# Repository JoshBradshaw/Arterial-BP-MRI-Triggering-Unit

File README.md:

# Arterial-BP-MRI-Triggering-Unit
Full source code and schematics for an Arterial Blood Pressure Pulse MRI triggering unit

A full description of each major component of this project is available at the [project website](http://joshbradshaw.github.io/Arterial-BP-MRI-Triggering-Unit/)

# This device is an arterial blood presure triggering unit for retrospective gating in MRI imaging.

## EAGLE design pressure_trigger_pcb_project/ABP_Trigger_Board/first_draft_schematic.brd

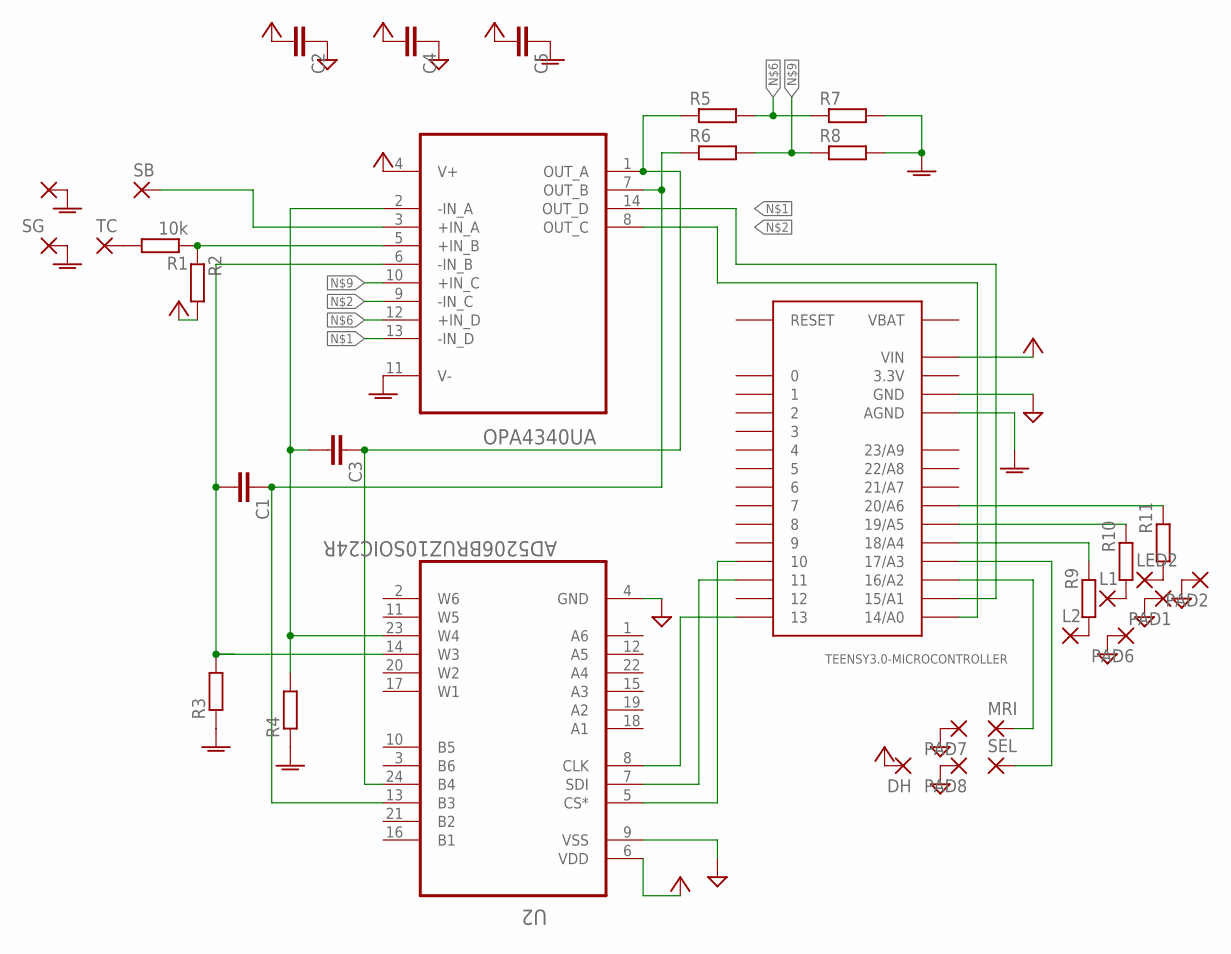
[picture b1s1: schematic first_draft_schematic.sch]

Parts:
C1, C3: 10pF; C0805
C2, C4, C5: 0.1uF; C0805
DH: WIREPAD1,6/0,9; 1,6/0,9
L1, L2: WIREPAD1,6/0,9; 1,6/0,9
LED2: WIREPAD1,6/0,9; 1,6/0,9
MRI: WIREPAD1,6/0,9; 1,6/0,9
PAD1, PAD2, PAD6, PAD7, PAD8: WIREPAD1,6/0,9; 1,6/0,9
R1, R2: 10k; R0805
R3, R4: 5k; R0805
R5, R6: 12k; R0805
R7, R8: 23.2k; R0805
R9, R10, R11: 681; R0805
SB: SAMBA; 1,6/0,9
SEL: WIREPAD1,6/0,9; 1,6/0,9
SG: WIREPAD1,6/0,9; 1,6/0,9
TC: WIREPAD1,6/0,9; 1,6/0,9
TEENSY3.0-MICROCONTROLLER: TEENSY_3.0_BASIC-PGM
TG: WIREPAD1,6/0,9; 1,6/0,9
U1: OPA4340UA; SOIC127P600X175-14N
U2: AD5206BRUZ10SOIC24R; SO24R

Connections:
3.3V: TEENSY3.0-MICROCONTROLLER.3.3V, TEENSY3.0-MICROCONTROLLER.3.3V1 (3.3V)
AGND: C5.1, R3.1, R4.1, R7.2, R8.2, SG.1, TEENSY3.0-MICROCONTROLLER.AGND, TG.1, U1.11 (V-)
GND: C2.1, C4.1, PAD1.1, PAD2.1, PAD6.1, PAD7.1, PAD8.1, TEENSY3.0-MICROCONTROLLER.GND, TEENSY3.0-MICROCONTROLLER.GND1 (GND), U2.4 (GND), U2.9 (VSS)
unnamed: TEENSY3.0-MICROCONTROLLER.15/A1, U1.13 (-IN_D), U1.14 (OUT_D)
unnamed: TEENSY3.0-MICROCONTROLLER.14/A0, U1.8 (OUT_C), U1.9 (-IN_C)
unnamed: C3.2, R4.2, U1.2 (-IN_A), U2.23 (W4)
unnamed: R1.1, R2.1, U1.5 (+IN_B)
unnamed: C3.1, R5.1, U1.1 (OUT_A), U2.24 (B4)
unnamed: R5.2, R7.1, U1.12 (+IN_D)
unnamed: TEENSY3.0-MICROCONTROLLER.10, U2.5 (CS*)
unnamed: TEENSY3.0-MICROCONTROLLER.11, U2.7 (SDI)
unnamed: R6.2, R8.1, U1.10 (+IN_C)
unnamed: SB.1, U1.3 (+IN_A)
unnamed: L2.1, R9.1
unnamed: C1.2, R3.2, U1.6 (-IN_B), U2.14 (W3)
unnamed: R1.2, TC.1
unnamed: R9.2, TEENSY3.0-MICROCONTROLLER.18/A4
unnamed: MRI.1, TEENSY3.0-MICROCONTROLLER.16/A2
unnamed: SEL.1, TEENSY3.0-MICROCONTROLLER.17/A3
unnamed: C1.1, R6.1, U1.7 (OUT_B), U2.13 (B3)
unnamed: L1.1, R10.1
unnamed: TEENSY3.0-MICROCONTROLLER.13, U2.8 (CLK)
unnamed: R10.2, TEENSY3.0-MICROCONTROLLER.19/A5
unnamed: LED2.1, R11.1
unnamed: R11.2, TEENSY3.0-MICROCONTROLLER.20/A6
VBAT: TEENSY3.0-MICROCONTROLLER.VBAT
VCC: C2.2, C4.2, C5.2, DH.1, R2.2, TEENSY3.0-MICROCONTROLLER.VIN, U1.4 (V+), U2.6 (VDD)

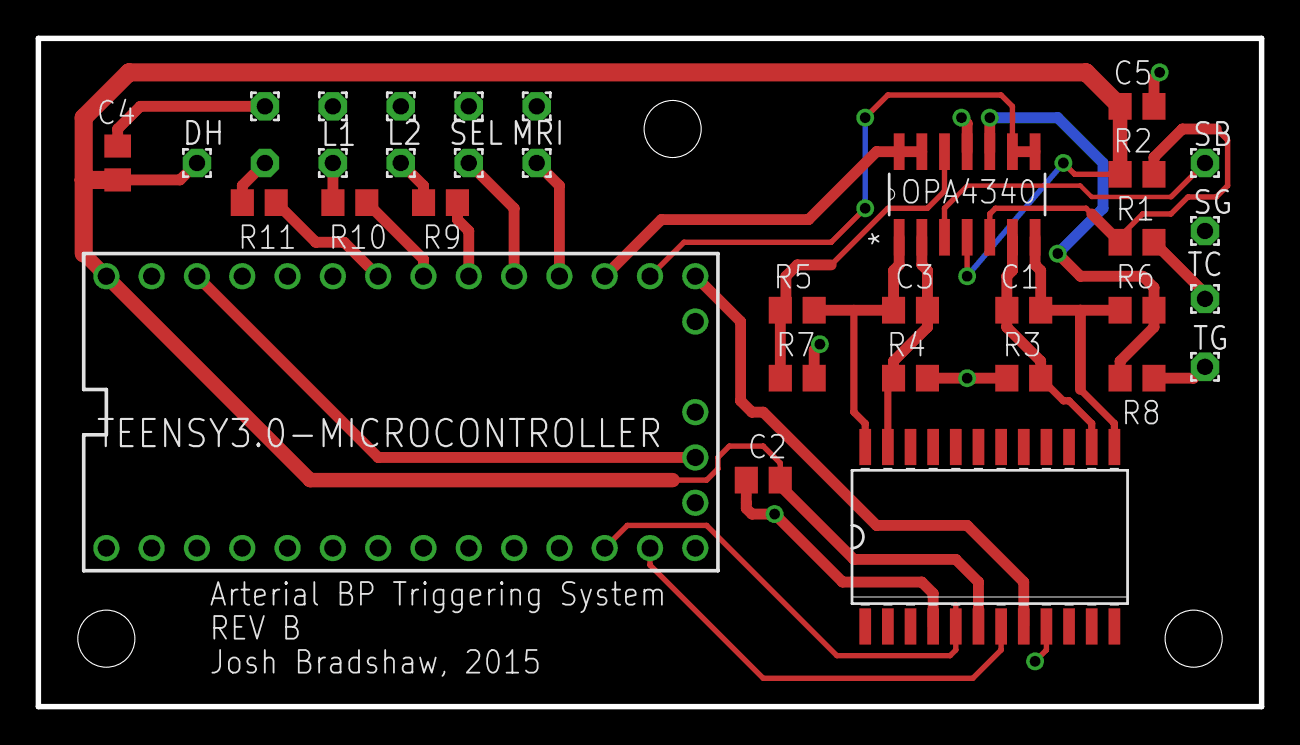
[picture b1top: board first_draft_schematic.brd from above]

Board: 2 copper layers, 68.6 x 37.5 mm, 34 parts (1 on the bottom side), 26 nets.

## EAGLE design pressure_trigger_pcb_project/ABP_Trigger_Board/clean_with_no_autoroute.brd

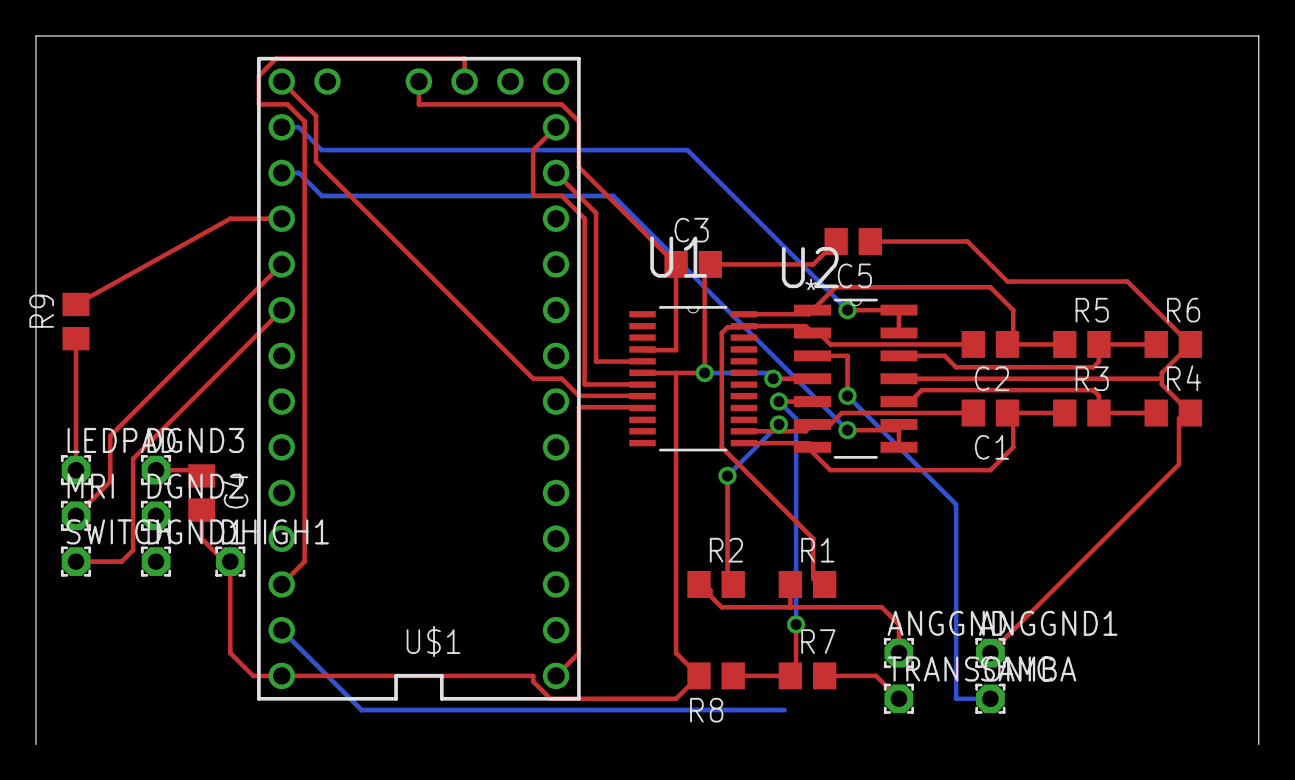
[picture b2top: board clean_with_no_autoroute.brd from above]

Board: 2 copper layers, 67.9 x 39.4 mm, 28 parts (0 on the bottom side), 22 nets.

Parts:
ANGGND, ANGGND1: WIREPAD1,6/0,9; 1,6/0,9
C1, C2: 10pF; C0805
C3, C4, C5: 0.1uF; C0805
DGND1, DGND2, DGND3: WIREPAD1,6/0,9; 1,6/0,9
DHIGH1: WIREPAD1,6/0,9; 1,6/0,9
LEDPAD: WIREPAD1,6/0,9; 1,6/0,9
MRI: WIREPAD1,6/0,9; 1,6/0,9
R1, R2: 5k; R0805
R3, R5: 12k; R0805
R4, R6: 23.2k; R0805
R7, R8: 10k; R0805
R9: 681; R0805
SAMBA: SAMBA; 1,6/0,9
SWITCH: WIREPAD1,6/0,9; 1,6/0,9
TRANSONIC: WIREPAD1,6/0,9; 1,6/0,9
U1: AD5206BRUZ10; SOP65P640X120-24N
U2: OPA4340UA; SOIC127P600X175-14N
U$1: TEENSY_3.0_BASIC-PGM

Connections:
3.3V: U$1.3.3V, U$1.3.3V1
AGND: ANGGND.1, ANGGND1.1, C5.1, R1.1, R2.1, R4.2, R6.2, U2.11, U$1.AGND
GND: C3.1, C4.1, DGND1.1, DGND2.1, DGND3.1, U1.4, U1.9, U$1.GND, U$1.GND1
unnamed: U2.13, U2.14, U$1.14/A0
unnamed: U2.8, U2.9, U$1.15/A1
unnamed: C2.2, R1.2, U1.23, U2.2
unnamed: R7.1, R8.1, U2.5
unnamed: C2.1, R5.1, U1.24, U2.1
unnamed: R5.2, R6.1, U2.12
unnamed: U1.5, U$1.10
unnamed: U1.7, U$1.11
unnamed: R3.2, R4.1, U2.10
unnamed: SAMBA.1, U2.3
unnamed: LEDPAD.1, R9.1
unnamed: C1.2, R2.2, U1.14, U2.6
unnamed: R7.2, TRANSONIC.1
unnamed: R9.2, U$1.16/A2
unnamed: MRI.1, U$1.17/A3
unnamed: SWITCH.1, U$1.18/A4
unnamed: C1.1, R3.1, U1.13, U2.7
unnamed: U1.8, U$1.13
VCC: C3.2, C4.2, C5.2, DHIGH1.1, R8.2, U1.6, U2.4, U$1.VIN

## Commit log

2015-02-11 Create gh-pages branch via GitHub
2015-02-13 made first docs post
2015-02-13 working teensy implementation of triggering algorithm that ran stable for 16 hours
2015-02-13 updated the site
2015-02-13 hopefully fixed url issues
2015-02-16 made the pages look pretty
2015-02-16 fixed config url
2015-02-16 please work this time you silly blog engine
2015-02-16 fixed relative URLS?
2015-02-16 ok now the urls work, but what about images
2015-02-16 another test
2015-02-16 image urls suck
2015-02-16 did spacing matter
2015-02-16 system check
2015-02-16 tried more stuff
2015-02-16 more stuff
2015-02-16 better
2015-02-16 does this work too?
2015-02-16 should be better
2015-02-17 added home page
2015-02-17 added more text
2015-02-17 designed algorithm for adjusting the pre-amp gain in real time
2015-02-19 first revision of schematic
2015-02-20 routed REV A of the board, silkscreen not yet done
2015-02-21 updated board fixed labels
2015-02-23 new board layout
2015-02-23 made finishing touching to the boards silkscreen and fattenned up the traces where I could
2015-02-23 integrated gain adjustment into the existing triggering software. Not throroughly tested yet, but seems to be working based on first glance
2015-02-23 schematic before package switch
2015-02-24 finalized board layout
2015-02-26 reorganized
2015-02-26 ditched all the useless eagle metadata files
2015-02-27 formatted code and removed unused sections
2015-02-27 changed readme
2015-02-27 wrote more stuff about PCB design
2015-02-27 fixed image link
2015-02-27 resized pcb layout image
2015-03-04 device fully functional, input selection feature added
2015-03-04 got GUI prototype working
2015-03-04 GUI prototype working
2015-03-05 plotting working well now
2015-03-05 refactored and wired up the UI
2015-03-05 refactor tested and working
2015-03-05 merged in gui_refactor branch
2015-03-06 fixed gitignore
2015-03-06 chaged the theme, looks prettier now
2015-03-06 fixed url
2015-03-06 fixed url?
2015-03-06 fixed the urls i hope
2015-03-06 fixed
2015-03-06 more fixed
2015-03-06 even more fixed
2015-03-06 super duper fixed
2015-03-06 all css links fixed
2015-03-06 fixed one image
2015-03-06 everything accounted for
2015-03-06 that had better be all the url problems
2015-03-06 that should actually cover it
2015-03-06 worth a try
2015-03-06 super fixed
2015-03-06 changed links
2015-03-06 revised overview page
2015-03-06 modified overview
2015-03-06 looking good
2015-03-06 touched up overview some more
2015-03-06 deleted sample posts
2015-03-09 changed to read the docs
2015-03-09 got mkdocs working?
2015-03-09 everything running stable, but there must be a bug in the peak threshold logic
2015-03-09 fixed ssf magnitude threshold bug
2015-03-10 wrote comments and docstrings
2015-03-10 renamed directories
2015-03-10 ran autoformat to fix the messy spacing
2015-03-10 made a really simple bill of materials
2015-03-11 cleaned up eagle directory, name things sensibly
2015-03-11 renamed eagle project
2015-03-12 wrote and revised documentation, improved logging in the monitoring tool
2015-03-12 finished documentation for now, tis a beautiful thing
2015-03-12 totally replaced the old site
2015-03-13 revised monitoring tool so that it will run on XP if required
2015-03-13 updated documentation
2015-03-13 wrote testing and validation page in documentation site
2015-03-13 updated docs site
2015-03-13 fixed code highlighting
2015-03-13 fixed image
2015-03-13 fixed site again
2015-03-26 state before trying to sensor working
2015-03-27 reverted peak thresholding algorithm to more basic version
2015-03-27 instrument functioning perfectly, code still a little messy
2015-03-30 formatted and cleaned up code
2015-03-30 reduced the amount of data sent over serial to ensure that it doesn't affect stability of the microcontroller
2015-03-30 everything working
2015-03-30 updated docs
2015-04-01 trouble with speed
2015-04-06 high speed triggering without bodging anything
2015-04-07 filter and ssf working awesome, something weird with peak detection using new filter
2015-04-07 fixed skipping issue
2015-04-07 working state
2015-04-07 fixed the way peak update works
2015-04-07 fixed sample buffering
2015-04-07 generally working, magnitude thresholds questionable
2015-04-08 skipping issue fixed and regression tested
2015-04-10 revised code comments, fixed indentation
2015-04-13 all set for surgery
2015-04-17 the first experiment was sucessful! updated documentation and stuff
2015-04-21 revised docs to use better figures
